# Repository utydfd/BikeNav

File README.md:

# BikeNav
An GPS navigation(originally intended for biking) with an E-ink screen, ESP32-S3 MCU and an SD card.
This repository contains code for the Arduino project and an Android app, as well as a PCB designed in KiCad and a case designed in Fusion 360.

## Map format
It uses standard raster 256x256px map tiles, right now from OSM, but can be changed to others.
The tiles are saved on the SD card in a ```ZOOM_LEVEL/X/Y.tile``` folder structure as 1 bit bitmap images.

## Data flow

Either import a GPX track or plan right inside the app(right now using project OSRM API), it downloads the required map tiles and saves them.

I can pick a trip from the main screen and send it over to the ESP via BLE, first the GPX is sent and then the tiles. They are converted from PNG to bitmap, compressed using RLE for faster transfers. The ESP is saving them to the SD card as they come. It’s also appending an index of tiles, which is sent from the ESP to the app, so that only the missing tiles are sent.

## ESPs software

The home screen contains smartphone like icons to "apps". The main one is obviously the map, which by default shows the current location. Pressing options brings up list of saved trips, clicking on it shows the preview and i can also start the navigation.

When navigating, the map rotates based on the upcoming GPX track; it shows the next turn distance and turn arrow(just calculated based on the angle of the turn). There are also screens for the progress and elevation graph. The GPX is loaded into PSRAM *(512kb allocated)* and PSRAM is also used for caching the map tiles *(~6MB allocated)*.

Other apps include the speedometer, phone(which has music controls along with battery %), weather(phone fetches from an API the forecast and also rain radar images), tracker(for recording GPX tracks), info(was used for debugging, has GPS, SD and battery statuses) and also mines and snake games. Those are not ideal but playable on the E-ink.

## Hardware

Its on a custom PCB, a standard 2 layer one. There are 2 regulators, one powering the ESP and other parts and the other solely for powering the front light - it has the EN pin connected to a GPIO so its controlled in software. The GPS module is connected via UART and also has an EN pin controllable. Micro SD card and the display are connected via SPI to the ESP. There is a TP4056 chip for charging, without the LEDs - its connected to the ESP so it can know the charging status.

For control, there is a rotary encoder(with a button) and 4 more buttons. The battery voltage is monitored with the ESP.

## BOM
- [Display](https://www.aliexpress.com/item/1005005183232092.html)
- [GP-02 GPS module](https://www.aliexpress.com/item/1005008117586848.html)
- [ESP32-S3 wroom module](https://www.aliexpress.com/item/1005004639132852.html)
- [SPX3819M5 LDO 3V3 regulator](https://www.aliexpress.com/item/1005004418830711.html)
- [2.2uF ceramic capacitors](https://www.aliexpress.com/item/1005002769519482.html)
- [15mm rotary endoder](https://www.aliexpress.com/item/1631706397.html)
- [USB-C breakout module](https://www.aliexpress.com/item/1005008296556115.html)

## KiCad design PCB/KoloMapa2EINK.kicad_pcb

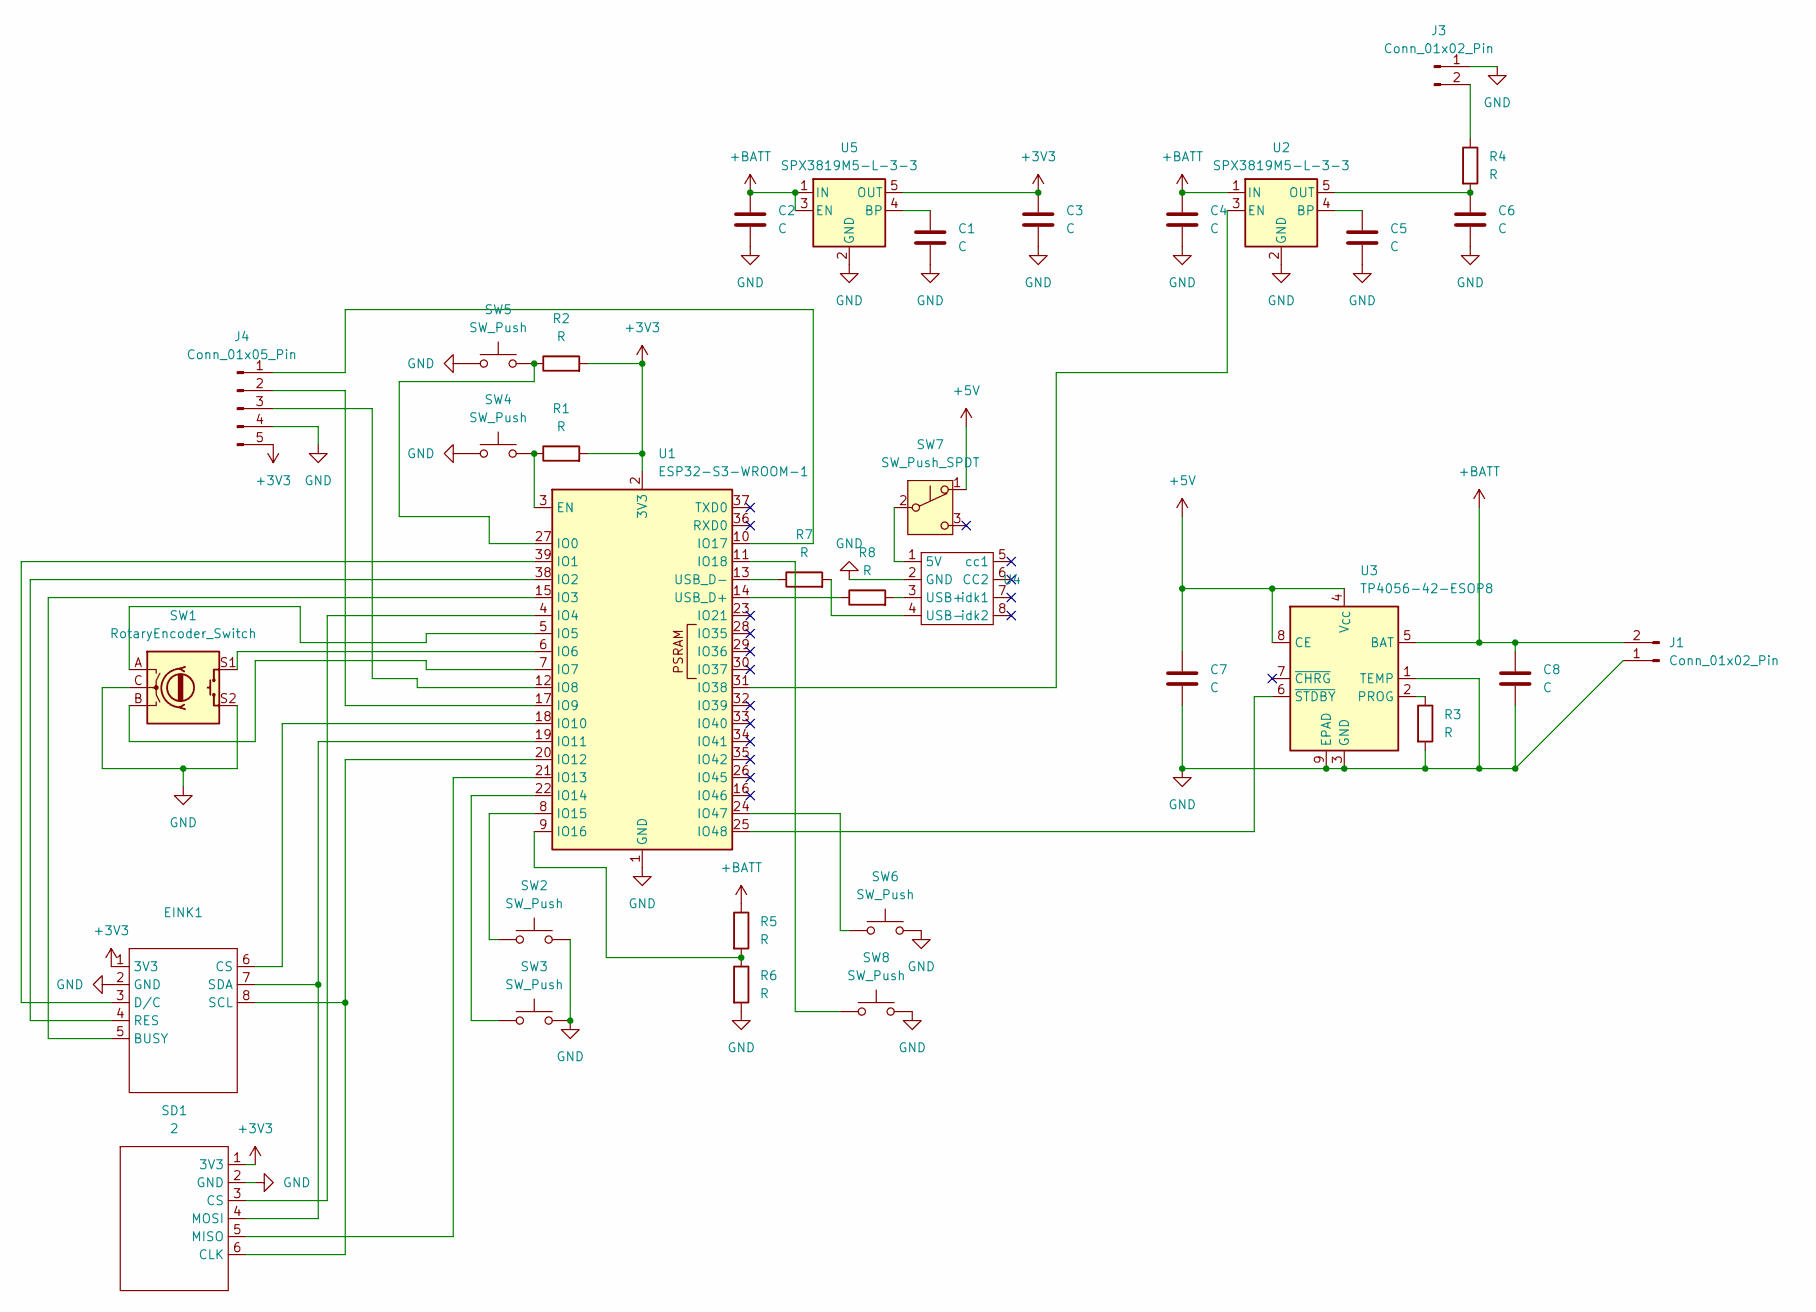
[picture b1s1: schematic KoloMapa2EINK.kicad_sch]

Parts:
C1, C2, C3, C4, C5, C6: C; C_1206_3216Metric_Pad1.33x1.80mm_HandSolder
C7: C; C_0402_1005Metric
C8: C; C_0504_1310Metric
EINK1: EINK
J1, J3: Conn_01x02_Pin; PinHeader_1x02_P2.54mm_Vertical
J4: Conn_01x05_Pin; PinHeader_1x05_P2.00mm_Vertical
R1, R2, R4, R5, R6: R; R_Axial_DIN0207_L6.3mm_D2.5mm_P10.16mm_Horizontal
R3: R; R_0402_1005Metric
R7, R8: R; R_Axial_DIN0207_L6.3mm_D2.5mm_P2.54mm_Vertical
SD1: 2; SD
SW1: RotaryEncoder_Switch; RotaryEncoder_Alps_EC11E-Switch_Vertical_H20mm
SW2, SW3, SW4, SW5, SW6, SW8: SW_Push; SW_PUSH_6mm
SW7: SW_Push_SPDT; SW_Slide_SPDT_Straight_CK_OS102011MS2Q
U1: ESP32-S3-WROOM-1
U2, U5: SPX3819M5-L-3-3; SOT-23-5
U3: TP4056-42-ESOP8; SOIC-8-1EP_3.9x4.9mm_P1.27mm_EP2.41x3.3mm_ThermalVias
U4: Untitled

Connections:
+3V3: C3.1, EINK1.1 (3V3), J4.5, R1.2, R2.2, SD1.1 (3V3), U1.2 (3V3), U5.5 (OUT)
+5V: C7.1, SW7.1 (A), U3.4 (V_{CC}), U3.8 (CE)
+BATT: C2.1, C4.1, C8.1, J1.2, R5.1, U2.1 (IN), U3.5 (BAT), U5.1 (IN), U5.3 (EN)
GND: C1.2, C2.2, C3.2, C4.2, C5.2, C6.2, C7.2, C8.2, EINK1.2 (GND), J1.1, J3.1, J4.4, R3.2, R6.2, SD1.2 (GND), SW1.C, SW1.S2, SW2.2, SW3.2, SW4.1, SW5.1, SW6.2, SW8.2, U1.1 (GND), U1.40 (GND), U1.41 (GND), U2.2 (GND), U3.1 (TEMP), U3.3 (GND), U3.9 (EPAD), U4.2 (GND), U5.2 (GND)
unnamed: EINK1.5 (BUSY), U1.15 (IO3)
unnamed: EINK1.6 (CS), U1.18 (IO10)
unnamed: EINK1.3 (D/C), U1.39 (IO1)
unnamed: EINK1.4 (RES), U1.38 (IO2)
unnamed: EINK1.8 (SCL), SD1.6 (CLK), U1.20 (IO12)
unnamed: EINK1.7 (SDA), SD1.4 (MOSI), U1.19 (IO11)
unnamed: J3.2, R4.1
unnamed: J4.1, U1.10 (IO17)
unnamed: J4.2, U1.17 (IO9)
unnamed: J4.3, U1.12 (IO8)
unnamed: SD1.3 (CS), U1.4 (IO4)
unnamed: SD1.5 (MISO), U1.21 (IO13)
unnamed: SW7.2 (B), U4.1 (5V)
unnamed: R1.1, SW4.2, U1.3 (EN)
unnamed: R2.1, SW5.2, U1.27 (IO0)
unnamed: SW1.A, U1.5 (IO5)
unnamed: SW1.S1, U1.6 (IO6)
unnamed: SW1.B, U1.7 (IO7)
unnamed: SW3.1, U1.22 (IO14)
unnamed: SW2.1, U1.8 (IO15)
unnamed: R5.2, R6.1, U1.9 (IO16)
unnamed: SW8.1, U1.11 (IO18)
unnamed: U1.31 (IO38), U2.3 (EN)
unnamed: SW6.1, U1.24 (IO47)
unnamed: U1.25 (IO48), U3.6 (~STDBY)
unnamed: R8.1, U1.14 (USB_D+)
unnamed: R7.1, U1.13 (USB_D-)
unnamed: C5.1, U2.4 (BP)
unnamed: C6.1, R4.2, U2.5 (OUT)
unnamed: R3.1, U3.2 (PROG)
unnamed: R8.2, U4.3 (USB+)
unnamed: R7.2, U4.4 (USB-)
unnamed: C1.1, U5.4 (BP)

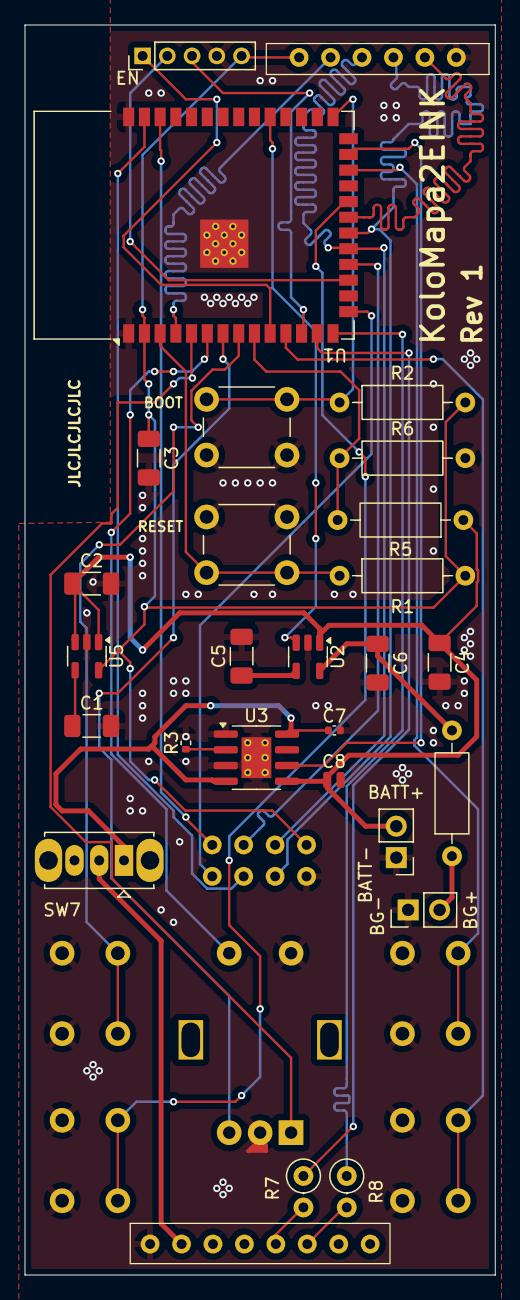
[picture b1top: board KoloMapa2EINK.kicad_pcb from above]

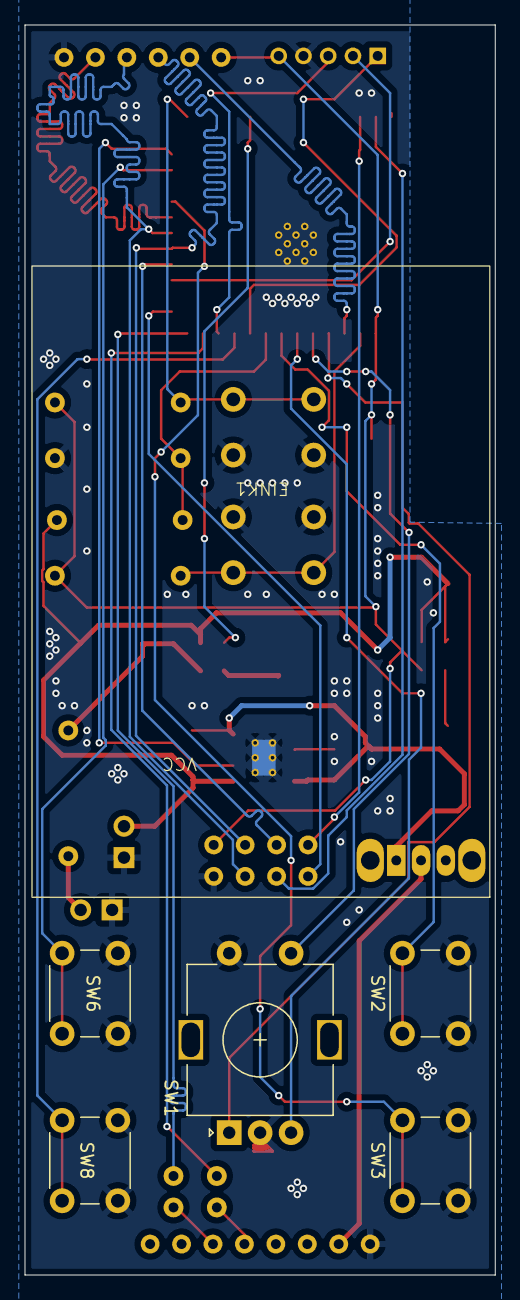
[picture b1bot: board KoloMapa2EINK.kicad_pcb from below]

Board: 2 copper layers, 38.0 x 101.0 mm, 34 parts (6 on the bottom side), 37 nets.

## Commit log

2026-01-27 Enhance README with project details and components
    Expanded project description and added details about components and files included in the repository.
2026-02-12 Update README to clarify repository contents
    Removed mention of STL files and PCB design from the repository description.
2026-03-10 Enhance README with detailed project information
    Expanded the README to include details about data flow, ESP software, hardware specifications, and bill of materials.
2026-03-10 Fix grammar and improve clarity in README.md
    Corrected grammar and phrasing in the README file for clarity.
2026-03-12 Update README to clarify project components
    Expanded repository description to include PCB and case designs.
2026-04-03 Update BOM with new components and links
